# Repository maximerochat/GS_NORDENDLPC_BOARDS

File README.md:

# LPC Hardware repository
This repo is made to host all hardware design of the LPC

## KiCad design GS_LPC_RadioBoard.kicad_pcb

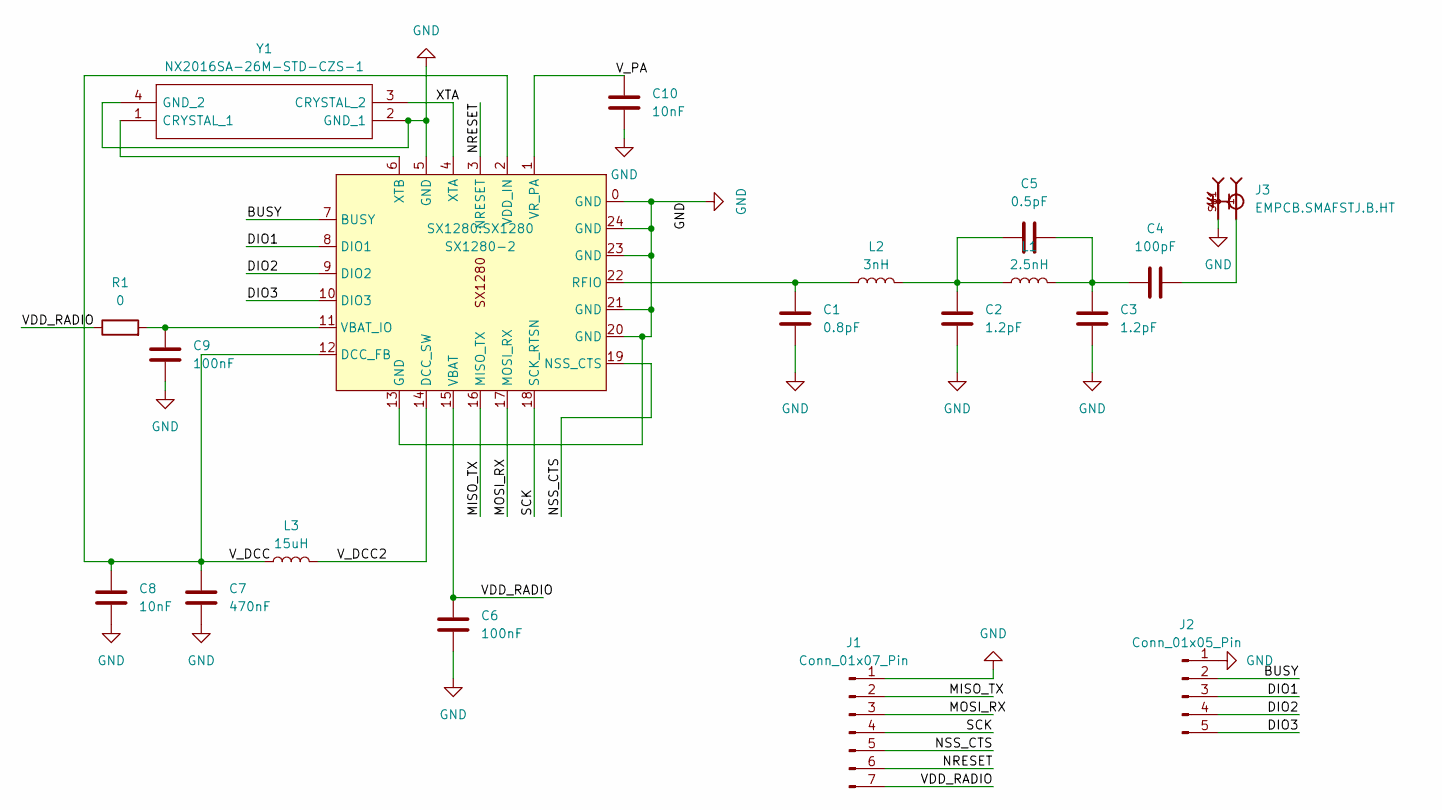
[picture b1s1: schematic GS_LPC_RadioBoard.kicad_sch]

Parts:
C1: 0.8pF; C_0402_1005Metric
C2, C3: 1.2pF; C_0402_1005Metric
C4: 100pF; C_0402_1005Metric
C5: 0.5pF; C_0402_1005Metric
C6, C9: 100nF; C_0402_1005Metric
C7: 470nF; C_0402_1005Metric
C8, C10: 10nF; C_0402_1005Metric
J1: Conn_01x07_Pin; PinHeader_1x07_P2.00mm_Vertical
J2: Conn_01x05_Pin; PinHeader_1x05_P2.00mm_Vertical
J3: EMPCB.SMAFSTJ.B.HT; TAOGLAS_EMPCB.SMAFSTJ.B.HT
L1: 2.5nH; L_0402_1005Metric
L2: 3nH; L_0402_1005Metric
L3: 15uH; L_0805_2012Metric
R1: 0; R_0402_1005Metric
SX1280-2: SX1280
Y1: NX2016SA-26M-STD-CZS-1; NX2016SA26MSTDCZS1; Mouser Part Number 344-NX2016SA26MSTZS1

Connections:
/BUSY: J2.2, SX1280-2.7 (BUSY)
/DIO1: J2.3, SX1280-2.8 (DIO1)
/DIO2: J2.4, SX1280-2.9 (DIO2)
/DIO3: J2.5, SX1280-2.10 (DIO3)
/MISO_TX: J1.2, SX1280-2.16 (MISO_TX)
/MOSI_RX: J1.3, SX1280-2.17 (MOSI_RX)
/NRESET: J1.6, SX1280-2.3 (NRESET)
/NSS_CTS: J1.5, SX1280-2.19 (NSS_CTS)
/SCK: J1.4, SX1280-2.18 (SCK_RTSN)
/VDD_RADIO: C6.1, J1.7, R1.1, SX1280-2.15 (VBAT)
/V_DCC: C7.1, C8.1, L3.1, SX1280-2.2 (VDD_IN), SX1280-2.12 (DCC_FB)
/V_DCC2: L3.2, SX1280-2.14 (DCC_SW)
/V_PA: C10.1, SX1280-2.1 (VR_PA)
/XTA: SX1280-2.4 (XTA), Y1.3 (CRYSTAL_2)
GND: C1.2, C2.2, C3.2, C6.2, C7.2, C8.2, C9.2, C10.2, J1.1, J2.1, J3.SH1, J3.SH2, J3.SH3, J3.SH4, SX1280-2.0 (GND), SX1280-2.5 (GND), SX1280-2.13 (GND), SX1280-2.20 (GND), SX1280-2.21 (GND), SX1280-2.23 (GND), SX1280-2.24 (GND), Y1.2 (GND_1), Y1.4 (GND_2)
unnamed: C2.1, C5.1, L1.1, L2.2
unnamed: C3.1, C4.1, C5.2, L1.2
unnamed: C4.2, J3.1
unnamed: C1.1, L2.1, SX1280-2.22 (RFIO)
unnamed: C9.1, R1.2, SX1280-2.11 (VBAT_IO)
unnamed: SX1280-2.6 (XTB), Y1.1 (CRYSTAL_1)

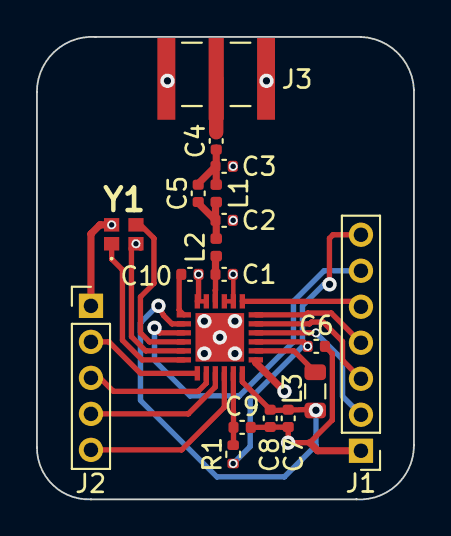
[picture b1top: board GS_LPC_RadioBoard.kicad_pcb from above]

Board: 2 copper layers, 20.9 x 25.7 mm, 19 parts (0 on the bottom side), 21 nets.

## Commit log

2024-01-03 finish first wiring
2024-01-03 version with minor adjustement
